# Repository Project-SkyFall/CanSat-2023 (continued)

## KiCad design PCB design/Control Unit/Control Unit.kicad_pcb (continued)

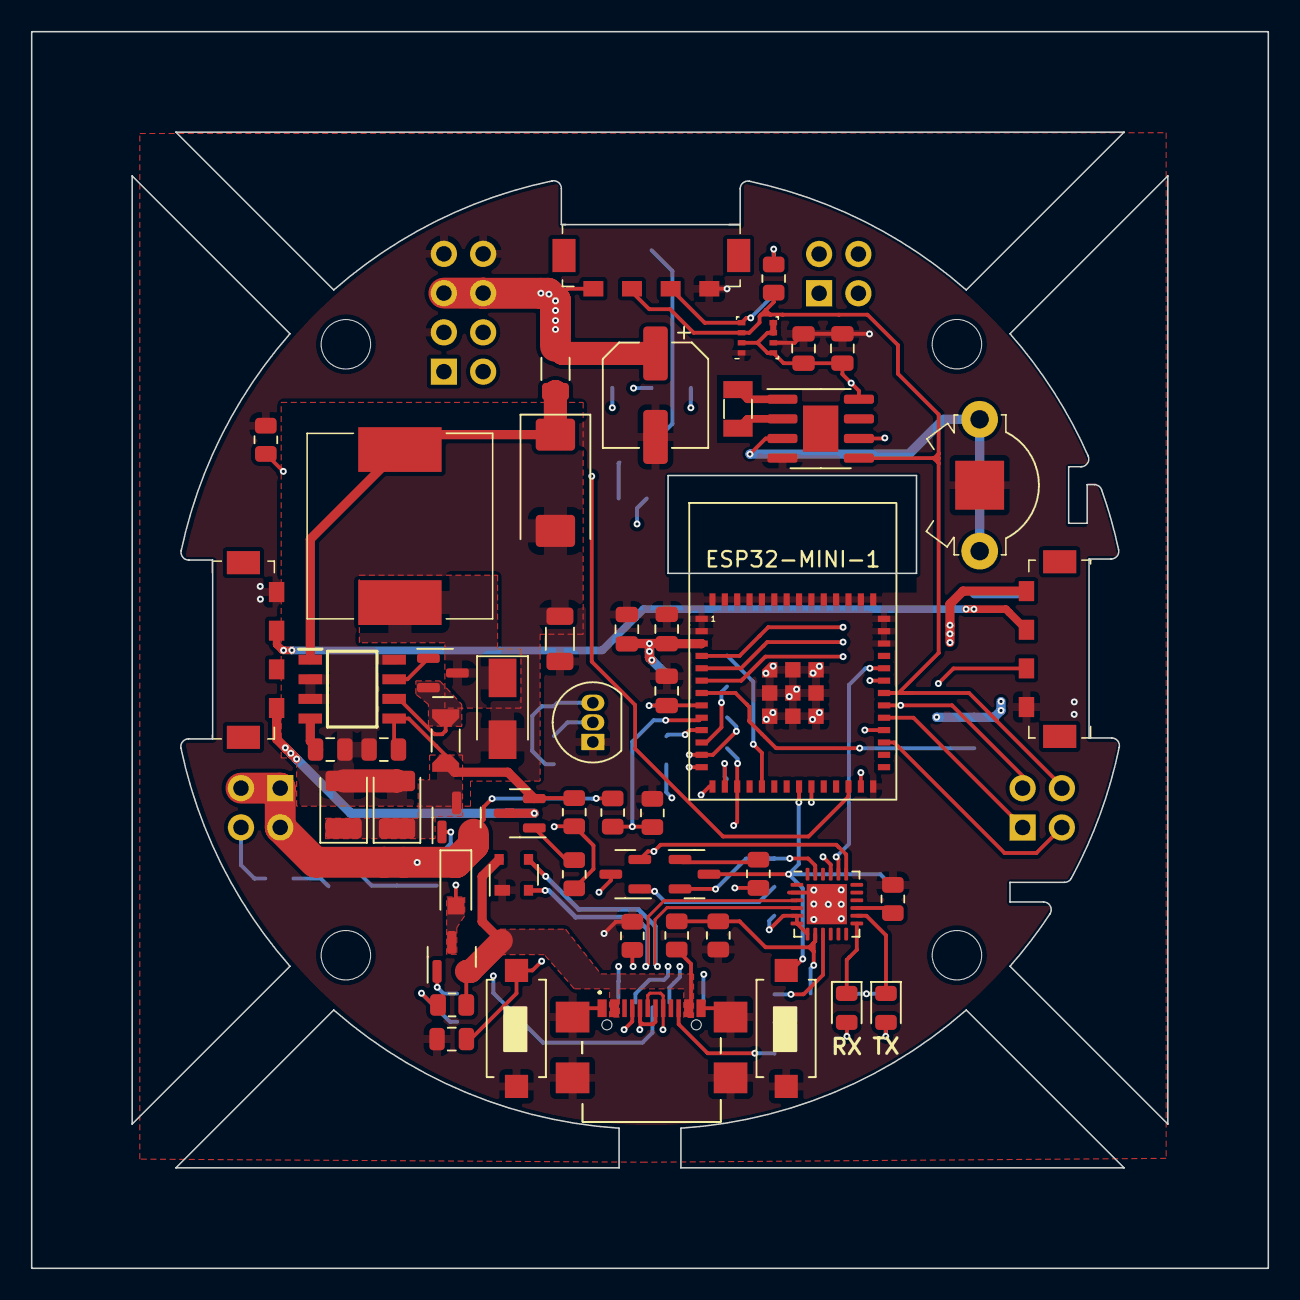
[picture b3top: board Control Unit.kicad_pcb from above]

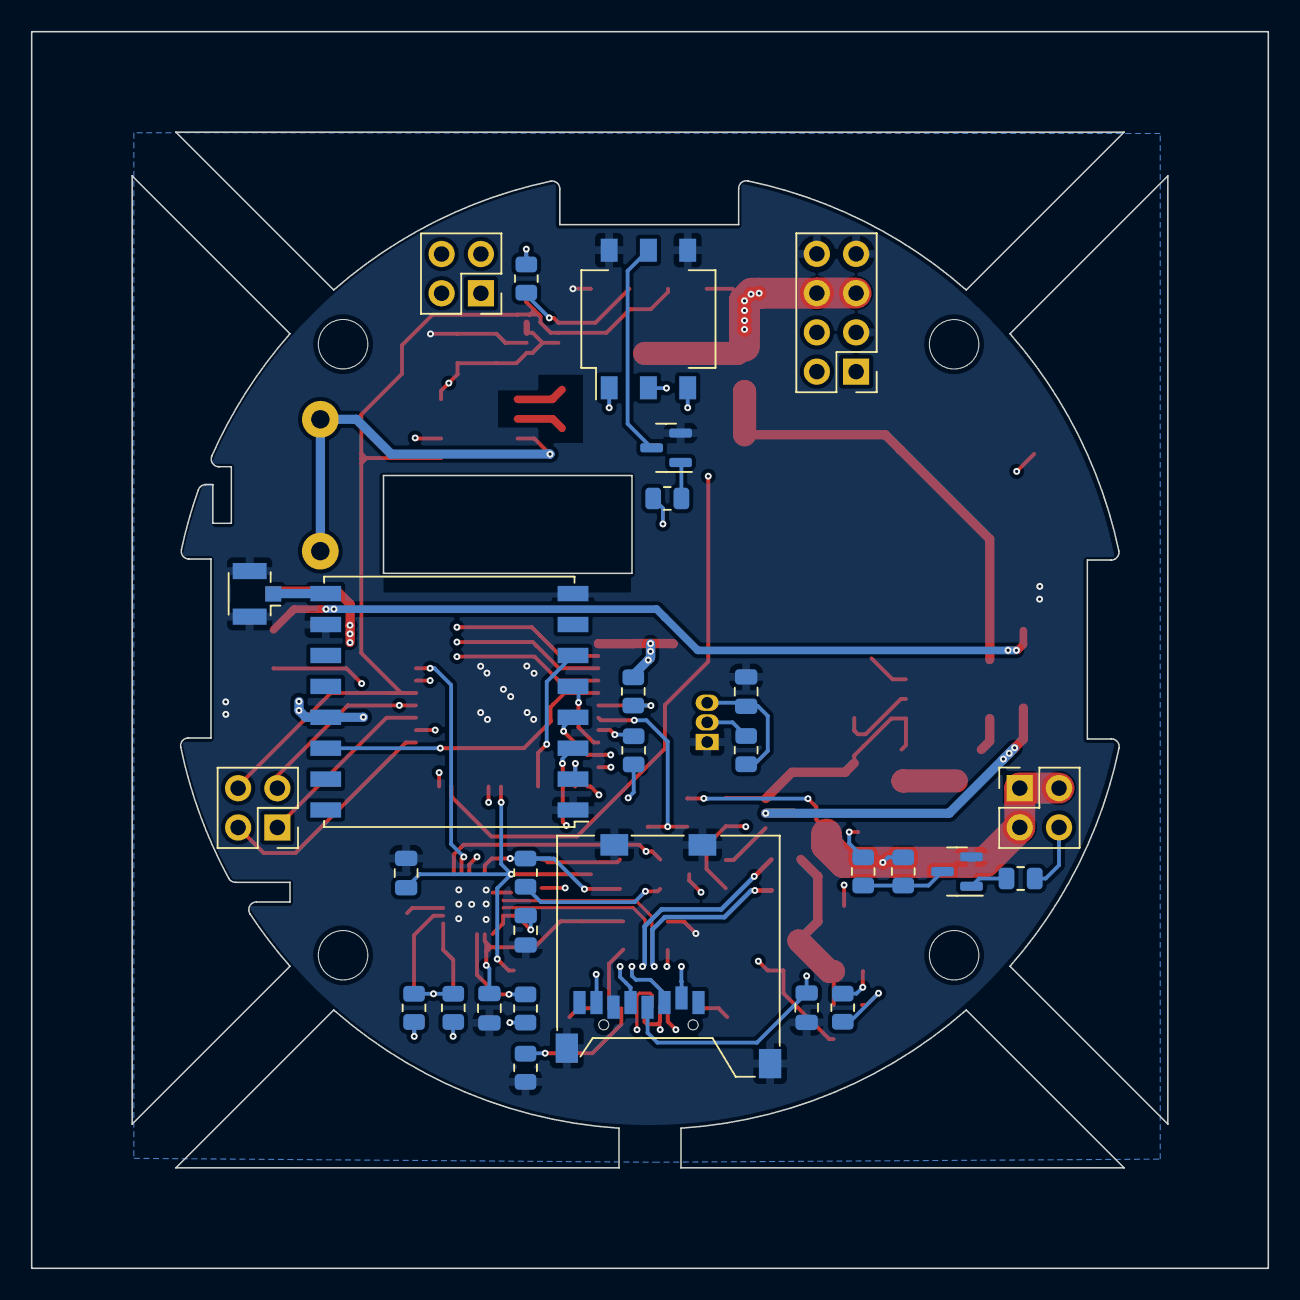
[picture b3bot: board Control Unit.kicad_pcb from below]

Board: 4 copper layers, 80.0 x 80.0 mm, 86 parts (29 on the bottom side), 68 nets.

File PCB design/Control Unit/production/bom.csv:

Designator,Footprint,Quantity,Value,LCSC Part #
AE401,U.FL_Hirose_U.FL-R-SMT-1_Vertical,1,Antenna_Shield,
BT701,2989,1,Backup battery,
"C201, C206",C_0805_2012Metric,2,10uF,
"C202, C208",C_0805_2012Metric,2,1uF,
C203,CP_Elec_6.3x7.7,1,680uF,
"C204, C205, C207, C504, C601",C_0805_2012Metric,5,0.1uF,
"C301, C302, C303",C_0805_2012Metric,3,100nF,
"C501, C502",CP_EIA-3528-21_Kemet-B,2,TPSB686K010R0600,
C503,C_0805_2012Metric,1,0.47uF,
C505,CP_EIA-7343-31_Kemet-D,1,293D227X9010D2TE3,
D201,D_SOD-123F,1,SBR3U40S1F-7,
"D202, D203",LED_0805_2012Metric,2,APT2012LSECK/J4-PRV,
D204,SOT-143,1,SP0503BAHT,
D501,D_SMA,1,B330A,
IC501,SOIC127P600X175-8N,1,MAX1626ESA+T,
J101,PinHeader_2x04_P2.54mm_Vertical,1,Conn_02x04_Male,
"J102, J103, J104",PinHeader_2x02_P2.54mm_Vertical,3,Conn_02x02_Male,
"J105, J106, J107",009155004541006,3,009155004541006,
J201,USB4110GFA,1,USB4110-GF-A,
J601,DS1139-05,1,Micro_SD_Card 823-046,
L501,CDRH125101MC,1,CDRH125NP-220MC,
"Q201, Q203, Q207, Q501",SOT-23,4,SI2305CDS-T1-BE3,
"Q202, Q204, Q205, Q206",SOT-23,4,BC847,
R201,R_0805_2012Metric,1,1k,
R202,R_0805_2012Metric,1,22k1,
"R203, R209, R214, R222",R_0805_2012Metric,4,100k,
"R204, R205, R206, R210, R211, R224, R225, R226",R_0805_2012Metric,8,10k,
R207,R_0805_2012Metric,1,47k5,
R208,R_0805_2012Metric,1,27k,
R212,R_0805_2012Metric,1,47k,
"R213, R502",R_1206_3216Metric,2,0R,
"R215, R216",R_0805_2012Metric,2,750R,
"R217, R218, R219",R_0805_2012Metric,3,5k1,
"R220, R221, R223",R_0805_2012Metric,3,5k,
R301,R_0805_2012Metric,1,4k7,
R501,R_1206_Current,1,PE1206FRE470R04L,
SW201,SW_DIP_SPSTx03_Slide_Omron_A6S-310x_W8.9mm_P2.54mm,1,DS04-254-1-03BK-SMT,
"SW202, SW203",Tlačítko SMD LaskaKit,2,LaskaKit tlačítko,
U201,QFN-24-1EP_4x4mm_P0.5mm_EP2.6x2.6mm,1,CP2102N-Axx-xQFN24,
U202,ESP32-MINI-1,1,ESP32-MINI-1,
U301,TO-92_Inline,1,DS18B20,
U302,Bosch_LGA-8_2.5x2.5mm_P0.65mm_ClockwisePinNumbering,1,BME280,
U401,HOPERF_RFM9XW_SMD,1,RFM96W-433S2,
U701,SOIC-8-1EP_3.9x4.9mm_P1.27mm_EP2.29x3mm,1,PT7C4339,
Y701,ECX-31B,1,ECS-.327-6-34B-C-TR,

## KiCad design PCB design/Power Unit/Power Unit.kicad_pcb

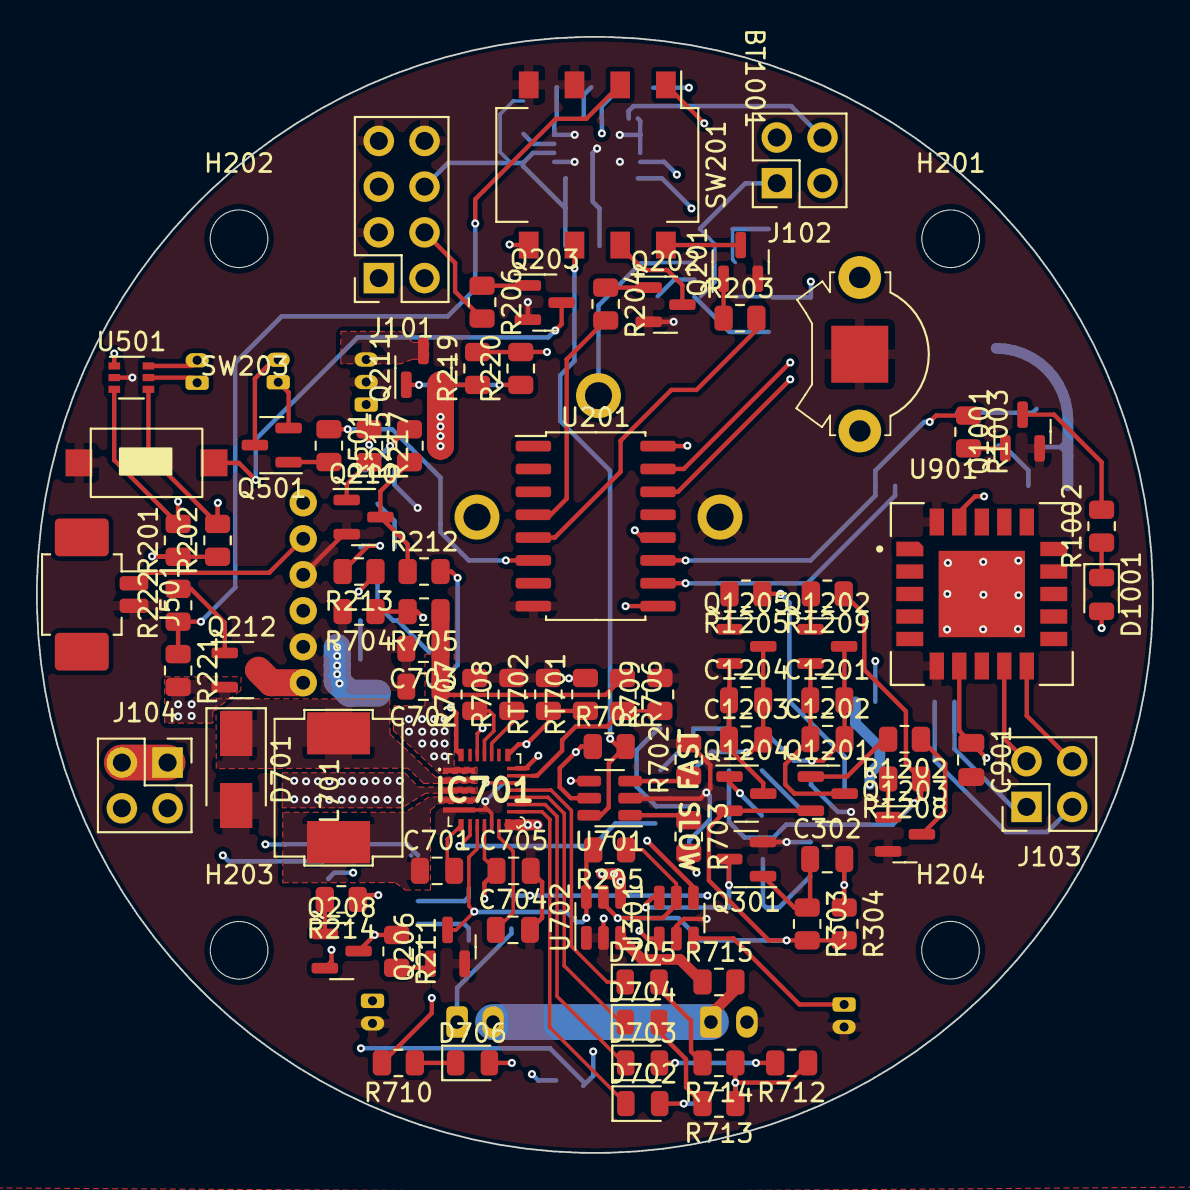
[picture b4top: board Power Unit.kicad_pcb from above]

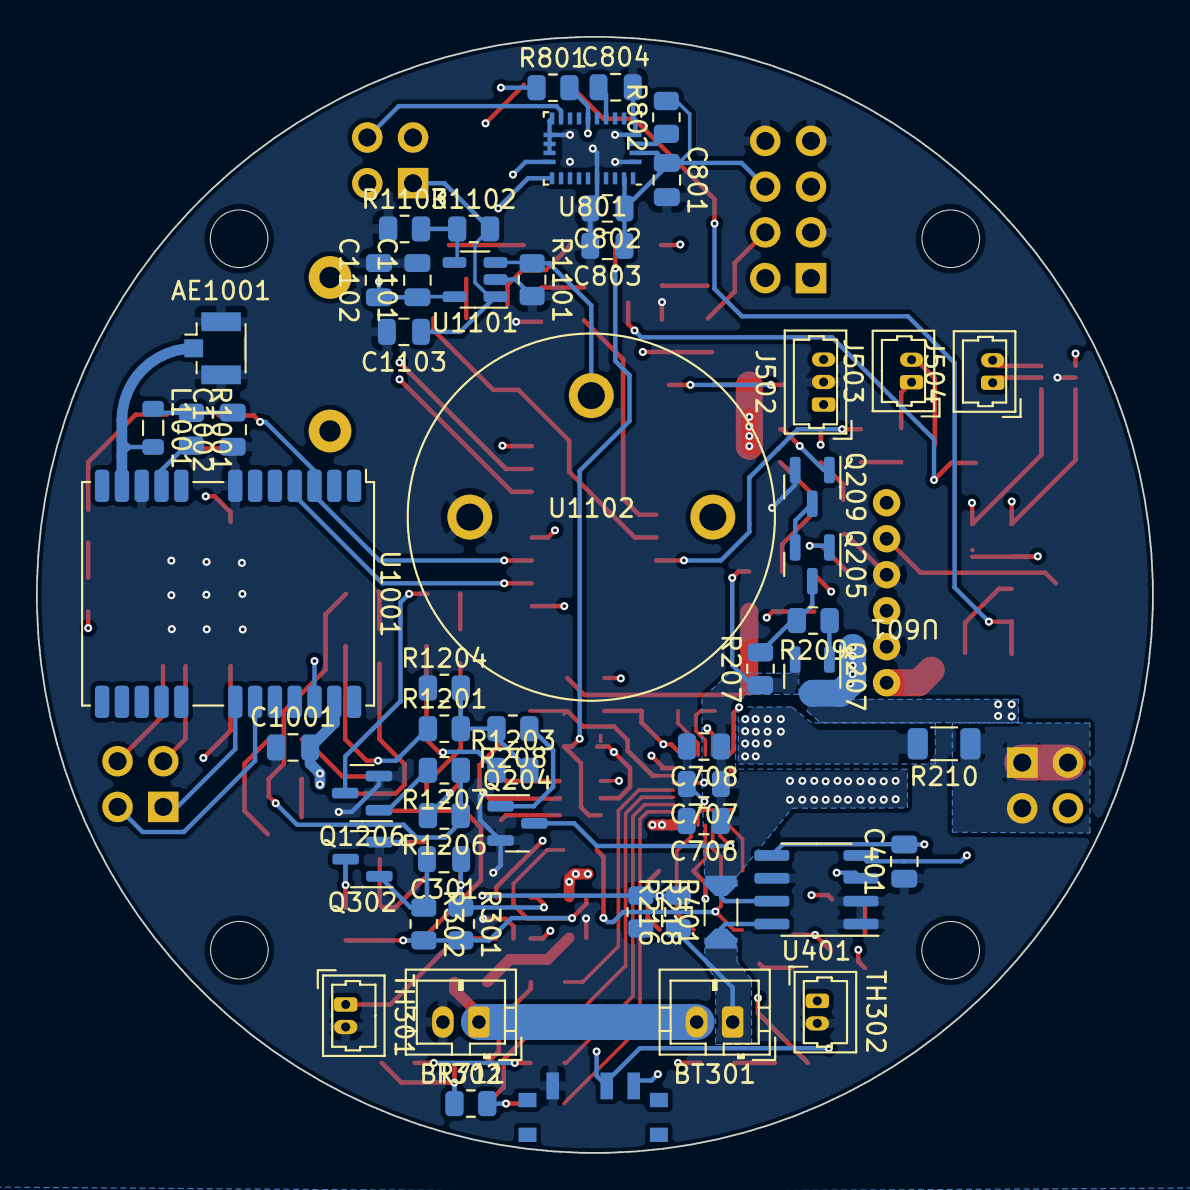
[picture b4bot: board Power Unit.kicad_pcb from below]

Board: 4 copper layers, 62.0 x 62.0 mm, 152 parts (57 on the bottom side), 113 nets.

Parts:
AE1001: Antenna_Shield; U.FL_Hirose_U.FL-R-SMT-1_Vertical
BT301, BT302: Battery_Cell; JST_PH_B2B-PH-K_1x02_P2.00mm_Vertical
BT1001: Backup battery; 2989
C301, C302, C1203, C1204: 22u; C_0805_2012Metric
C401, C1202: 10u; C_0805_2012Metric
C701: 0.1uF; C_0805_2012Metric
C702, C706, C707: 22uF; C_0805_2012Metric
C703: 4.7uF; C_0805_2012Metric
C704: C; C_0805_2012Metric
C705: 1u; C_0805_2012Metric
C708, C1001: 1uF; C_0805_2012Metric
C801: 120n; C_0805_2012Metric
C802: 6n8; C_0805_2012Metric
C803, C804: 100n; C_0805_2012Metric
C901, C1002, C1101: 100nF; C_0805_2012Metric
C1102: 10uF; C_0805_2012Metric
C1103: 10nF; C_0805_2012Metric
C1201: NC; C_0805_2012Metric
D701: B330A; D_SMA
D702, D703, D704, D705: APT2012LZGCK; LED_0805_2012Metric
D706: APT2012LSECK/J3-PRV; LED_0805_2012Metric
D1001: APT2012LSECK/J4-PRV; LED_0805_2012Metric
H201, H202, H203, H204: MountingHole; MountingHole_3.2mm_M3
IC701: MP2639AGR-Z; MP2639AGRZ
J101: Conn_02x04_Female; PinSocket_2x04_P2.54mm_Vertical
J102, J103, J104: Conn_02x02_Female; PinSocket_2x02_P2.54mm_Vertical
J501: Conn_01x02; Molex_PicoBlade_53261-0271_1x02-1MP_P1.25mm_Horizontal
J502: Conn_01x03; Molex_PicoBlade_53047-0310_1x03_P1.25mm_Vertical
J503, J504: Conn_01x02; Molex_PicoBlade_53047-0210_1x02_P1.25mm_Vertical
L701: BMRA000606302R2MA1
L1001: 27nH; L_0805_2012Metric
Q201, Q202, Q203, Q204, Q205, Q206, Q209, Q210, Q301, Q302, Q501, Q1001, Q1203, Q1206: BC847; SOT-23
Q207, Q211, Q212: SI2305CDS-T1-BE3; SOT-23
Q208, Q1201, Q1202, Q1204, Q1205: BC857; SOT-23
R201, R202, R205, R208, R209, R211, R220, R222, R301, R304, R701, R709, R801, R802, R1201: 10k; R_0805_2012Metric
R203, R204, R206, R214, R501, R1003: 5k; R_0805_2012Metric
R207, R212, R213, R215, R217, R219, R221, R1202, R1204, R1205, R1206, R1207, R1208, R1209: 100k; R_0805_2012Metric
R210: 0R; R_1206_3216Metric
R216: 12k; R_0805_2012Metric
R218: 5k1; R_0805_2012Metric
R302, R303: 220k; R_0805_2012Metric
R401: PE1206FRE470R04L; R_1206_Current
R702: 82k; R_0805_2012Metric
R703: 820k; R_0805_2012Metric
R704, R705: R; R_0805_2012Metric
R706: 27k4; R_0805_2012Metric
R707: 143k; R_0805_2012Metric
R708: 75k; R_0805_2012Metric
R710, R712, R713, R714: 330R; R_0805_2012Metric
R711, R1002: 750R; R_0805_2012Metric
R715: 0R5; R_0805_2012Metric
R1001: 10R; R_0805_2012Metric
R1101, R1103: 100R; R_0805_2012Metric
R1102: 20k; R_0805_2012Metric
R1203: 15k; R_0805_2012Metric
RT701: 1k87; R_0805_2012Metric
RT702: 5k11; R_0805_2012Metric
SW201: DS04-254-1-04BK-SMT; SW_DIP_SPSTx04_Slide_Omron_A6S-410x_W8.9mm_P2.54mm
SW202: PCM12SMTR
SW203: LaskaKit tlačítko; Tlačítko SMD LaskaKit
TH301, TH302: NRBE104J3435B2J; Molex_PicoBlade_53047-0210_1x02_P1.25mm_Vertical
U201: PCA8574D; SO-16_5.3x10.2mm_P1.27mm
U301, U701, U702: TS5A3159DBV; SOT-23-6
U401: INA219AxD; SOIC-8_3.9x4.9mm_P1.27mm
U501: MCP4017-xxxxLT; SOT-363_SC-70-6
U601: TBS_UNIFY_PRO32_5G8_nano; TBS UNIFY PRO32 5G8 nano
U801: BNO055; LGA-28_5.2x3.8mm_P0.5mm
U901: SCD41; XDCR_SCD41-D-R2
U1001: NEO-M9N; ublox_NEO
U1101: OPA333xxDBV; SOT-23-5
U1102: ME2-02; ME2-O2

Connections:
/Power Unit/BATT_INT: J101.4, R206.2
/Power Unit/BAT_SENSE: J102.2, R216.2, R218.1
/Power Unit/Battery Pack/BAT_M: BT301.2 (-), BT302.1 (+), R715.2
/Power Unit/Battery Pack/NTC: IC701.20 (NTC), RT701.1, RT702.1, U301.4
/Power Unit/Battery Pack/NTC_SWITCH: C301.1, Q301.3 (C), R301.1, U301.6
/Power Unit/CAMTRANS-FET: Q207.3 (D), Q211.2 (S), Q212.2 (S), R219.1, R221.2
/Power Unit/CAM_CONTROL: R501.1, U201.6 (P2)
/Power Unit/CH_SLOW/FAST: R701.2, SW201.6, U701.6
/Power Unit/Camera transmit/VIDEO: J501.1, J502.1, U601.5 (Video)
/Power Unit/Camera transmit/V_IN: Q212.3 (D), U601.1 (V_{IN})
/Power Unit/Camera/V_IN: J502.3, Q211.3 (D)
/Power Unit/D delay/OUT: R208.2, R1201.2, R1203.2, R1204.2
/Power Unit/EXTINT_{GPS}: U201.10 (P5), U1001.4 (EXTINT)
/Power Unit/FPV_{SM_A}: J101.2, U601.6 (SA)
/Power Unit/GND: AE1001.2 (Shield), BT302.2 (-), BT1001.2 (-), C401.1, C702.2, C703.2, C704.2, C705.2, C706.2, C707.2, C708.2, C801.2, C802.2, C803.2, C804.2, C901.2, C1001.1, C1002.1, C1101.2, C1102.2, C1103.2, D701.2 (A), IC701.5 (PGND), IC701.10 (AGND), J101.3, J101.7, J101.8, J501.2, J502.2, Q201.2 (E), Q202.2 (E), Q203.2 (E), Q204.2 (E), Q206.2 (E), Q209.2 (E), Q210.2 (E), Q301.2 (E), Q302.2 (E), Q1001.2 (E), Q1203.2 (E), Q1206.2 (E), R218.2, R702.2, R703.2, R704.2, R707.2, R708.2, R709.2, R1101.2, R1103.1, R1204.1, RT702.2, SW201.3, SW201.4, SW202.1 (A), SW203.1, TH301.2, TH302.2, U201.8 (VSS), U301.2 (GND), U401.1 (A1), U401.2 (A0), U401.6 (GND), U501.2 (VSS), U601.2 (GND), U601.4 (GND), U701.2 (GND), U702.1, U702.2 (GND), U801.2 (GND), U801.5 (PS1), U801.6 (PS0), U801.15 (GNDIO), U801.16 (GNDIO), U801.17 (COM3), U801.18 (COM2), U801.25 (GNDIO), U901.6 (GND), U901.20 (GND), U901.21 (GND), U1001.7 (VDD_USB), U1001.10 (GND), U1101.2 (V-), U1102.1 (OUT-)
/Power Unit/IMU_{INT}: J102.4, U801.14 (INT)
/Power Unit/IS_CHARGE: Q208.3 (C), R211.1, R217.1
/Power Unit/IS_USB: J101.1, Q208.2 (E)
/Power Unit/MODE_{CH}: IC701.8 (MODE), Q206.3 (C), R205.2, U201.9 (P4), U702.6
/Power Unit/M_SWITCH: J104.4, R213.1, R1206.1, R1207.1, R1208.1, R1209.1, SW202.2 (B)
/Power Unit/OXY_{OUT}: C1103.1, J102.1, R1102.2, U1101.1
/Power Unit/P_IN: BT301.1 (+), R216.1, R401.1, U401.8 (IN+)
/Power Unit/P_OUT: C706.1, C707.1, C708.1, IC701.3 (VH), Q207.2 (S), R207.1, R212.2, R401.2, U401.7 (IN-)
/Power Unit/RESET_{IMU}: R801.2, U201.12 (P7), U801.11 (~RESET)
/Power Unit/SCL: J103.3, R201.2, U201.14 (SCL), U401.4 (SCL), U501.3 (SCL), U801.19 (COM1), U901.9 (SCL)
/Power Unit/SCL_{2}/RXD: J103.2, U1001.19 (SCL/SPI_CLK)
/Power Unit/SDA: J103.4, R202.2, U201.15 (SDA), U401.3 (SDA), U501.4 (SDA), U801.20 (COM0), U901.10 (SDA)
/Power Unit/SDA_{2}/TXD: J103.1, U1001.18 (SDA/~SPI_CS)
/Power Unit/SW_CAMERA: R219.2, R220.2, SW201.1
/Power Unit/SW_CAMERA_{IO}: R204.2, U201.4 (P0)
/Power Unit/SW_CHARGE: R214.1, SW201.5
/Power Unit/SW_TRANSMIT: R221.1, R222.1, SW201.2
/Power Unit/SW_TRANSMIT_{IO}: R203.2, U201.5 (P1)
/Power Unit/Switch-mode battery charger/BST: C701.2, IC701.6 (BST)
/Power Unit/Switch-mode battery charger/FB: IC701.17 (FB), R704.1, R705.2
/Power Unit/Switch-mode battery charger/ILIM: IC701.24 (ILIM), U701.4
/Power Unit/Switch-mode battery charger/ISET: IC701.23 (ISET), R707.1
/Power Unit/Switch-mode battery charger/LX: D701.1 (K), IC701.2 (LX), L701.2
/Power Unit/Switch-mode battery charger/OLIM: IC701.22 (OLIM), R708.1
/Power Unit/Switch-mode battery charger/SW: C701.1, IC701.4 (SW), L701.1
/Power Unit/Switch-mode battery charger/TMR: C704.1, IC701.11 (TMR)
/Power Unit/Switch-mode battery charger/VL: C702.1, C703.1, IC701.1 (VL), R210.2, R705.1, R706.1
/Power Unit/Switch-mode battery charger/VLIM: IC701.18 (VLIM), R706.2, R709.1
/Power Unit/Switch-mode battery charger/VNTC: D706.2 (A), IC701.19 (VNTC), R711.1, R712.1, R713.1, R714.1, RT701.2
/Power Unit/Switch-mode battery charger/~CHG: IC701.26 (~CHG), R710.2
/Power Unit/Switch-mode battery charger/~PB: IC701.7 (~PB), Q203.3 (C), Q204.3 (C), SW203.2
/Power Unit/TIMEPULSE_{GPS}: R1003.1, U201.11 (P6), U1001.3 (TIMEPULSE)
/Power Unit/VCC: C401.2, C801.1, C802.1, C803.1, C901.1, C1001.2, C1101.1, C1102.1, D1001.2 (A), J101.5, J101.6, R201.1, R202.1, R801.1, R802.2, U201.16 (VDD), U401.5 (VS), U501.1 (VDD), U801.3 (VDD), U801.28 (VDDIO), U901.7 (VDD), U901.19 (VDDH), U1001.23 (VCC), U1101.5 (V+)
/Power Unit/VCC_5V: J104.1, J104.2, J104.3, R210.1
/Power Unit/VCC_{BCK}: C705.1, IC701.9 (VCC), Q1201.2 (E), Q1204.2 (E), R205.1, R301.2, R302.2, R303.2, R304.2, R701.1, SW202.3 (C), U301.5 (V+), U701.5 (V+), U702.5 (V+)
unnamed: AE1001.1 (A), L1001.2, U1001.11 (RF_IN)
unnamed: BT1001.1 (+), U1001.22 (V_BCKP)
unnamed: C301.2, Q302.1 (B), R302.1
unnamed: C302.1, Q301.1 (B), R303.1
unnamed: C302.2, Q302.3 (C), R304.1
unnamed: C804.1, U801.9 (CAP)
unnamed: C1002.2, L1001.1, R1001.1
unnamed: C1201.1, C1202.1, Q1201.3 (C), Q1202.2 (E)
unnamed: C1201.2, C1202.2, Q1202.3 (C), R1201.1
unnamed: C1203.1, C1204.1, Q1204.3 (C), Q1205.2 (E)
unnamed: C1203.2, C1204.2, Q1205.3 (C), R1203.1
unnamed: D702.1 (K), IC701.13 (LED1)
unnamed: D702.2 (A), R711.2
unnamed: D703.1 (K), IC701.14 (LED2)
unnamed: D703.2 (A), R712.2
unnamed: D704.1 (K), IC701.15 (LED3)
unnamed: D704.2 (A), R713.2
unnamed: D705.1 (K), IC701.16 (LED4)
unnamed: D705.2 (A), R714.2
unnamed: D706.1 (K), R710.1
unnamed: D1001.1 (K), R1002.1
unnamed: IC701.12 (MIND), U702.4
unnamed: J503.1, Q501.2 (E)
unnamed: J503.2, Q501.3 (C)
unnamed: J504.1, U501.5 (B)
unnamed: J504.2, U501.6 (W)
unnamed: Q201.1 (B), R203.1
unnamed: Q201.3 (C), SW201.8
unnamed: Q202.1 (B), R204.1
unnamed: Q202.3 (C), SW201.7
unnamed: Q203.1 (B), R206.1
unnamed: Q204.1 (B), R208.1
unnamed: Q205.1 (B), R213.2
unnamed: Q205.2 (E), Q209.3 (C)
unnamed: Q205.3 (C), R207.2, R209.2
unnamed: Q206.1 (B), R211.2
unnamed: Q207.1 (G), R209.1
unnamed: Q208.1 (B), R214.2
unnamed: Q209.1 (B), R215.2
unnamed: Q210.1 (B), R217.2
unnamed: Q210.3 (C), R212.1, R215.1
unnamed: Q211.1 (G), R220.1
unnamed: Q212.1 (G), R222.2
unnamed: Q501.1 (B), R501.2
unnamed: Q1001.1 (B), R1003.2
unnamed: Q1001.3 (C), R1002.2
unnamed: Q1201.1 (B), R1202.2
unnamed: Q1202.1 (B), R1209.2
unnamed: Q1203.1 (B), R1208.2
unnamed: Q1203.3 (C), R1202.1
unnamed: Q1204.1 (B), R1206.2
unnamed: Q1205.1 (B), R1205.2
unnamed: Q1206.1 (B), R1207.2
unnamed: Q1206.3 (C), R1205.1
unnamed: R702.1, U701.3
unnamed: R703.1, U701.1
unnamed: R715.1, U702.3
unnamed: R802.1, U801.4 (~BOOT_LOAD_PIN)
unnamed: R1001.2, U1001.9 (VCC_RF)
unnamed: R1101.1, U1101.3 (+), U1102.2 (OUT)
unnamed: R1102.1, R1103.2, U1101.4 (-)
unnamed: TH301.1, U301.3
unnamed: TH302.1, U301.1

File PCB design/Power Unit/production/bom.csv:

Designator,Footprint,Quantity,Value,LCSC Part #
AE1001,U.FL_Hirose_U.FL-R-SMT-1_Vertical,1,Antenna_Shield,
BT1001,2989,1,Backup battery,
"BT301, BT302",JST_PH_B2B-PH-K_1x02_P2.00mm_Vertical,2,Battery_Cell,
"C1001, C705, C708",C_0805_2012Metric,3,1uF,
"C1002, C1101, C803, C804, C901",C_0805_2012Metric,5,100nF,
"C1102, C1202, C401",C_0805_2012Metric,3,10uF,
C1103,C_0805_2012Metric,1,10nF,
"C1203, C1204, C301, C302, C702, C706, C707",C_0805_2012Metric,7,22uF,
C701,C_0805_2012Metric,1,0.1uF,
C703,C_0805_2012Metric,1,4.7uF,
C704,C_0805_2012Metric,1,C,
C801,C_0805_2012Metric,1,120nF,
C802,C_0805_2012Metric,1,6n8,
D1001,LED_0805_2012Metric,1,APT2012LSECK/J4-PRV,
D701,D_SMA,1,B330A,
"D702, D703, D704, D705",LED_0805_2012Metric,4,APT2012LZGCK,
D706,LED_0805_2012Metric,1,APT2012LSECK/J3-PRV,
IC701,MP2639AGRZ,1,MP2639AGR-Z,
J101,PinSocket_2x04_P2.54mm_Vertical,1,Conn_02x04_Female,
"J102, J103, J104",PinSocket_2x02_P2.54mm_Vertical,3,Conn_02x02_Female,
J501,Molex_PicoBlade_53261-0271_1x02-1MP_P1.25mm_Horizontal,1,Conn_01x02,
J502,Molex_PicoBlade_53047-0310_1x03_P1.25mm_Vertical,1,Conn_01x03,
"J503, J504",Molex_PicoBlade_53047-0210_1x02_P1.25mm_Vertical,2,Conn_01x02,
L1001,L_0805_2012Metric,1,27nH,
L701,BMRA000606302R2MA1,1,BMRA000606302R2MA1,
"Q1001, Q1203, Q1206, Q201, Q202, Q203, Q204, Q205, Q206, Q209, Q210, Q301, Q302, Q501",SOT-23,14,BC847,
"Q1201, Q1202, Q1204, Q1205, Q208",SOT-23,5,BC857,
"Q207, Q211, Q212",SOT-23,3,SI2305CDS-T1-BE3,
R1001,R_0805_2012Metric,1,12R,
"R1002, R711",R_0805_2012Metric,2,750R,
"R1003, R203, R204, R206, R214, R501",R_0805_2012Metric,6,5k,
"R1101, R1103",R_0805_2012Metric,2,100R,
R1102,R_0805_2012Metric,1,20k,
"R1201, R201, R202, R205, R208, R209, R211, R220, R222, R301, R304, R701, R709, R801, R802",R_0805_2012Metric,15,10k,
"R1202, R1204, R1205, R1206, R1207, R1208, R1209, R207, R212, R213, R215, R217, R219, R221",R_0805_2012Metric,14,100k,
R1203,R_0805_2012Metric,1,15k,
R210,R_1206_3216Metric,1,0R,
R216,R_0805_2012Metric,1,12k,
R218,R_0805_2012Metric,1,5k1,
"R302, R303",R_0805_2012Metric,2,220k,
R401,R_1206_Current,1,PE1206FRE470R04L,
R702,R_0805_2012Metric,1,82k,
R703,R_0805_2012Metric,1,820k,
"R704, R705",R_0805_2012Metric,2,R,
R706,R_0805_2012Metric,1,27k4,
R707,R_0805_2012Metric,1,143k,
R708,R_0805_2012Metric,1,75k,
"R710, R712, R713, R714",R_0805_2012Metric,4,330R,
R715,R_0805_2012Metric,1,0R5,
RT701,R_0805_2012Metric,1,1k87,
RT702,R_0805_2012Metric,1,5k11,
"SW1001, SW1002",Cu_Conn,2,CU_CONN,
SW201,SW_DIP_SPSTx04_Slide_Omron_A6S-410x_W8.9mm_P2.54mm,1,DS04-254-1-04BK-SMT,
SW202,PCM12SMTR,1,PCM12SMTR,
SW203,Tlačítko SMD LaskaKit,1,LaskaKit tlačítko,
"TH301, TH302",Molex_PicoBlade_53047-0210_1x02_P1.25mm_Vertical,2,NRBE104J3435B2J,
U1001,ublox_NEO,1,NEO-M9N,
U1101,SOT-23-5,1,OPA333xxDBV,
U1102,ME2-O2,1,ME2-02,
U201,SO-16_5.3x10.2mm_P1.27mm,1,PCA8574D,
"U301, U701, U702",SOT-23-6,3,TS5A3159DBV,
U401,SOIC-8_3.9x4.9mm_P1.27mm,1,INA219AxD,
U501,SOT65P210X110-6N,1,AD5246,
U601,TBS UNIFY PRO32 5G8 nano,1,TBS_UNIFY_PRO32_5G8_nano,
U801,LGA-28_5.2x3.8mm_P0.5mm,1,BNO055,
U901,XDCR_SCD41-D-R2,1,SCD41,

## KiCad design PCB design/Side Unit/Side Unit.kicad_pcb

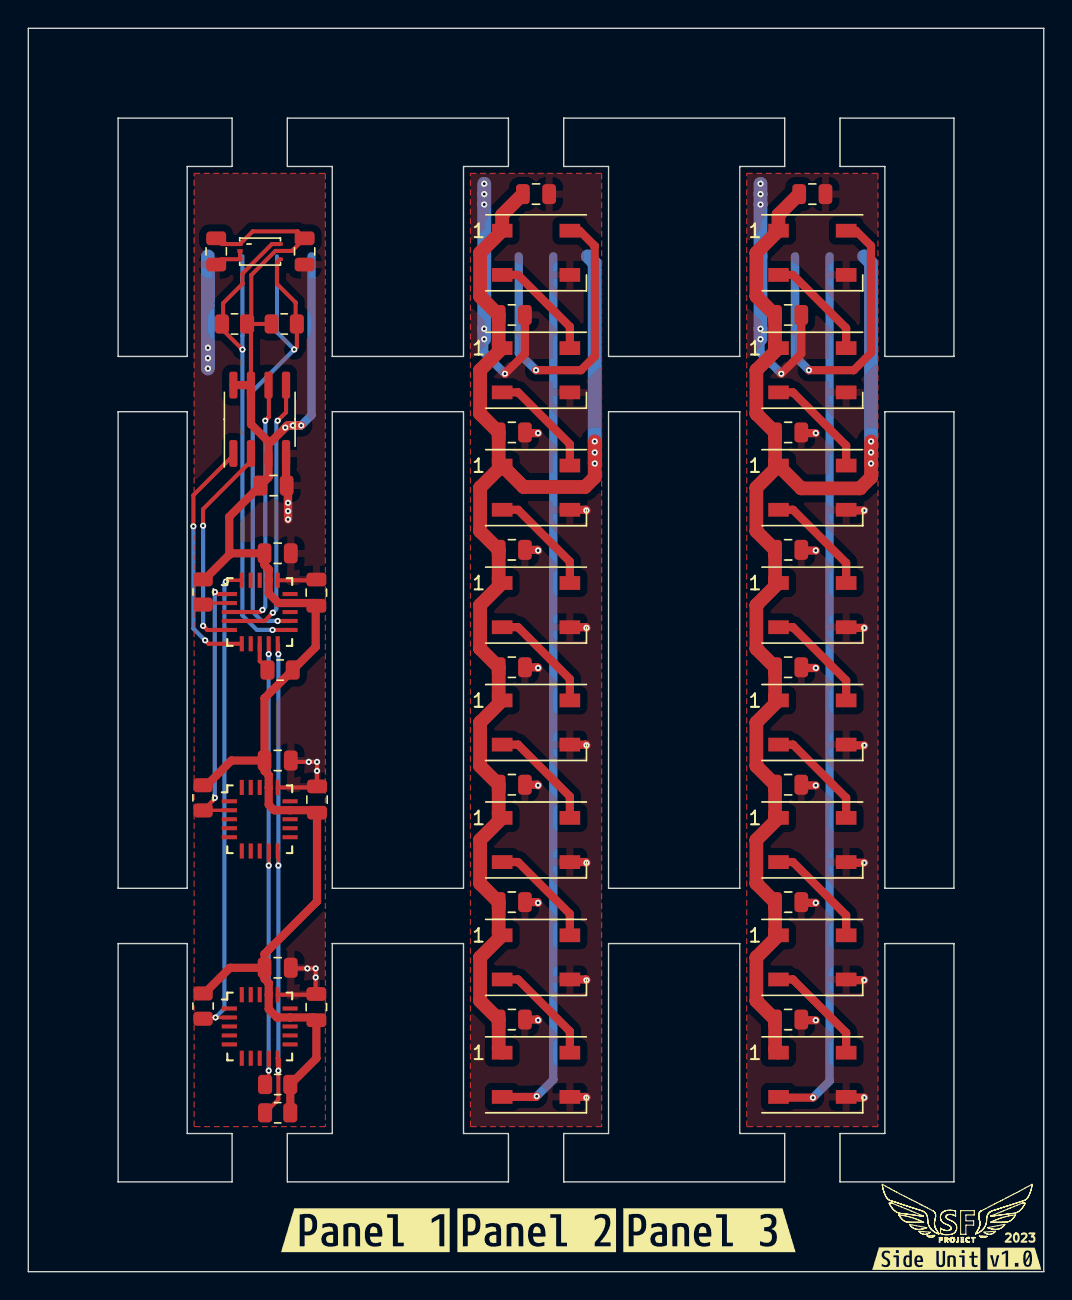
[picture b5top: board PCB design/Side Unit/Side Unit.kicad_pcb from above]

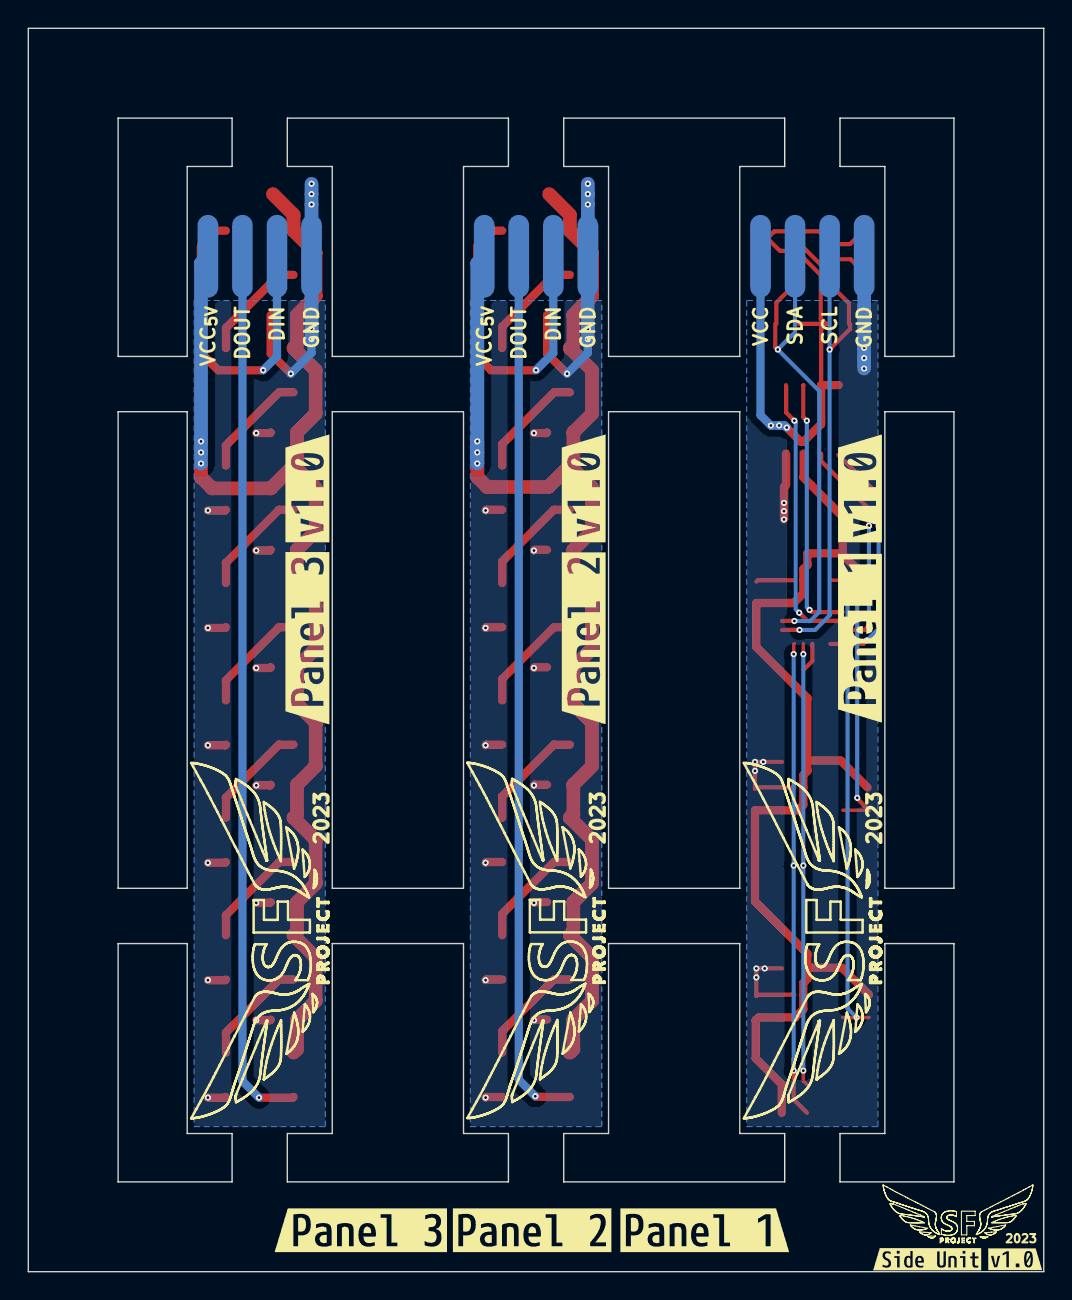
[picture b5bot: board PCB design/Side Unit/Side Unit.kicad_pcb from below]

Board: 2 copper layers, 73.5 x 90.0 mm, 73 parts (14 on the bottom side), 36 nets.

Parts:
C301, C302, C303, C304, C305, C306, C307, C308, C401, C402, C403, C404, C405, C406, C407, C408, C501, C503, C506, C601, C602: 100nF; C_0805_2012Metric
C502, C504, C505, C507: 1uF; C_0805_2012Metric
D301, D302, D303, D304, D305, D306, D307, D308, D401, D402, D403, D404, D405, D406, D407, D408: WS2812B; LED_WS2812B_PLCC4_5.0x5.0mm_P3.2mm
IC501: AT25SF041B-SSHD-B; SOIC-8_3.9x4.9mm_P1.27mm
J101, J102, J103: Land patern; Land-pattern
R201, R202, R501, R502, R503, R504, R506, R507: 10k; R_0805_2012Metric
U501: AS72651; AMS_LGA-20_4.7x4.5mm_P0.65mm
U502: AS72652; AMS_LGA-20_4.7x4.5mm_P0.65mm
U503: AS72653; AMS_LGA-20_4.7x4.5mm_P0.65mm
U601: BH1730; WSOF6
kibuzzard-63C42A2A: G***; kibuzzard-63C42A2A
kibuzzard-63C42A5F, kibuzzard-63C42A5F#2, kibuzzard-63C42A5F#3: G***; kibuzzard-63C42A5F
kibuzzard-63C42B4A: G***; kibuzzard-63C42B4A
kibuzzard-63C42B39: G***; kibuzzard-63C42B39
kibuzzard-63C86FC3: G***; kibuzzard-63C86FC3
kibuzzard-63C86FCE: G***; kibuzzard-63C86FCE
kibuzzard-63C685CC, kibuzzard-63C685CC#2: G***; kibuzzard-63C685CC
kibuzzard-63C685D8, kibuzzard-63C685D8#2: G***; kibuzzard-63C685D8
kibuzzard-63C6862F: G***; kibuzzard-63C6862F
kibuzzard-63C68642, kibuzzard-63C68642#2: G***; kibuzzard-63C68642
kibuzzard-63C68658: G***; kibuzzard-63C68658

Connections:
/Panel 1/GND: C501.2, C502.2, C503.2, C504.2, C505.2, C506.2, C507.2, C601.1, C602.2, IC501.4 (GND), J101.1, U501.16 (GND), U502.16 (GND), U503.16 (GND), U601.2 (INT), U601.3 (GND)
/Panel 1/SCL: J101.2, R202.2, U501.11 (RX/SCL_S), U601.6 (SCL)
/Panel 1/SDA: J101.3, R201.2, U501.12 (TX/SDA_S), U601.4 (SDA)
/Panel 1/Spectroscope Unit/MISO: IC501.2 (SO_(IO1_)), U501.5 (MISO)
/Panel 1/Spectroscope Unit/MOSI: IC501.5 (SI_(IO0_)), U501.4 (MOSI)
/Panel 1/Spectroscope Unit/SCK: IC501.6 (SCK), U501.3 (SCK)
/Panel 1/Spectroscope Unit/SCL_S: R504.2, U501.9 (SCL_M), U502.9 (SCL_S), U503.9 (SCL_S)
/Panel 1/Spectroscope Unit/SDA_S: R503.2, U501.10 (SDA_M), U502.10 (SDA_S), U503.10 (SDA_S)
/Panel 1/Spectroscope Unit/~CS: IC501.1 (~CS), U501.6 (~CS)
/Panel 1/Spectroscope Unit/~RES: R507.2, U501.2 (~RES)
/Panel 1/Spectroscope Unit/~SLV1_RES: R502.2, U501.1 (~SLV1_RES), U502.2 (~RES)
/Panel 1/Spectroscope Unit/~SLV2_RES: R501.2, U501.20 (~SLV2_RES), U503.2 (~RES)
/Panel 1/VCC: C501.1, C502.1, C503.1, C504.1, C505.1, C506.1, C507.1, C601.2, C602.1, IC501.3 (~WP_(IO2_)), IC501.7 (~HOLD_(IO3_)), IC501.8 (VCC), J101.4, R201.1, R202.1, R501.1, R502.1, R503.1, R504.1, R506.1, R507.1, U501.14 (VDD2), U501.17 (VDD1), U502.14 (VDD2), U502.17 (VDD1), U503.14 (VDD2), U503.17 (VDD1), U601.1 (VCC), U601.5 (DVI)
/Panel 2/DIN: D301.4 (DIN), J102.2
/Panel 2/DOUT: D308.2 (DOUT), J102.3
/Panel 2/GND: C301.1, C302.1, C303.1, C304.1, C305.1, C306.1, C307.1, C308.1, D301.3 (VSS), D302.3 (VSS), D303.3 (VSS), D304.3 (VSS), D305.3 (VSS), D306.3 (VSS), D307.3 (VSS), D308.3 (VSS), J102.1
/Panel 2/VCC_5V: C301.2, C302.2, C303.2, C304.2, C305.2, C306.2, C307.2, C308.2, D301.1 (VDD), D302.1 (VDD), D303.1 (VDD), D304.1 (VDD), D305.1 (VDD), D306.1 (VDD), D307.1 (VDD), D308.1 (VDD), J102.4
/Panel 3/DIN: D401.4 (DIN), J103.2
/Panel 3/DOUT: D408.2 (DOUT), J103.3
/Panel 3/GND: C401.1, C402.1, C403.1, C404.1, C405.1, C406.1, C407.1, C408.1, D401.3 (VSS), D402.3 (VSS), D403.3 (VSS), D404.3 (VSS), D405.3 (VSS), D406.3 (VSS), D407.3 (VSS), D408.3 (VSS), J103.1
/Panel 3/VCC_5V: C401.2, C402.2, C403.2, C404.2, C405.2, C406.2, C407.2, C408.2, D401.1 (VDD), D402.1 (VDD), D403.1 (VDD), D404.1 (VDD), D405.1 (VDD), D406.1 (VDD), D407.1 (VDD), D408.1 (VDD), J103.4
unnamed: D301.2 (DOUT), D302.4 (DIN)
unnamed: D302.2 (DOUT), D303.4 (DIN)
unnamed: D303.2 (DOUT), D304.4 (DIN)
unnamed: D304.2 (DOUT), D305.4 (DIN)
unnamed: D305.2 (DOUT), D306.4 (DIN)
unnamed: D306.2 (DOUT), D307.4 (DIN)
unnamed: D307.2 (DOUT), D308.4 (DIN)
unnamed: D401.2 (DOUT), D402.4 (DIN)
unnamed: D402.2 (DOUT), D403.4 (DIN)
unnamed: D403.2 (DOUT), D404.4 (DIN)
unnamed: D404.2 (DOUT), D405.4 (DIN)
unnamed: D405.2 (DOUT), D406.4 (DIN)
unnamed: D406.2 (DOUT), D407.4 (DIN)
unnamed: D407.2 (DOUT), D408.4 (DIN)
unnamed: R506.2, U501.8 (I2C_ENB)
